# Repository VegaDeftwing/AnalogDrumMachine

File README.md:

# AnalogDrumMachine
Capstone Project @ UNL, 2020-2021

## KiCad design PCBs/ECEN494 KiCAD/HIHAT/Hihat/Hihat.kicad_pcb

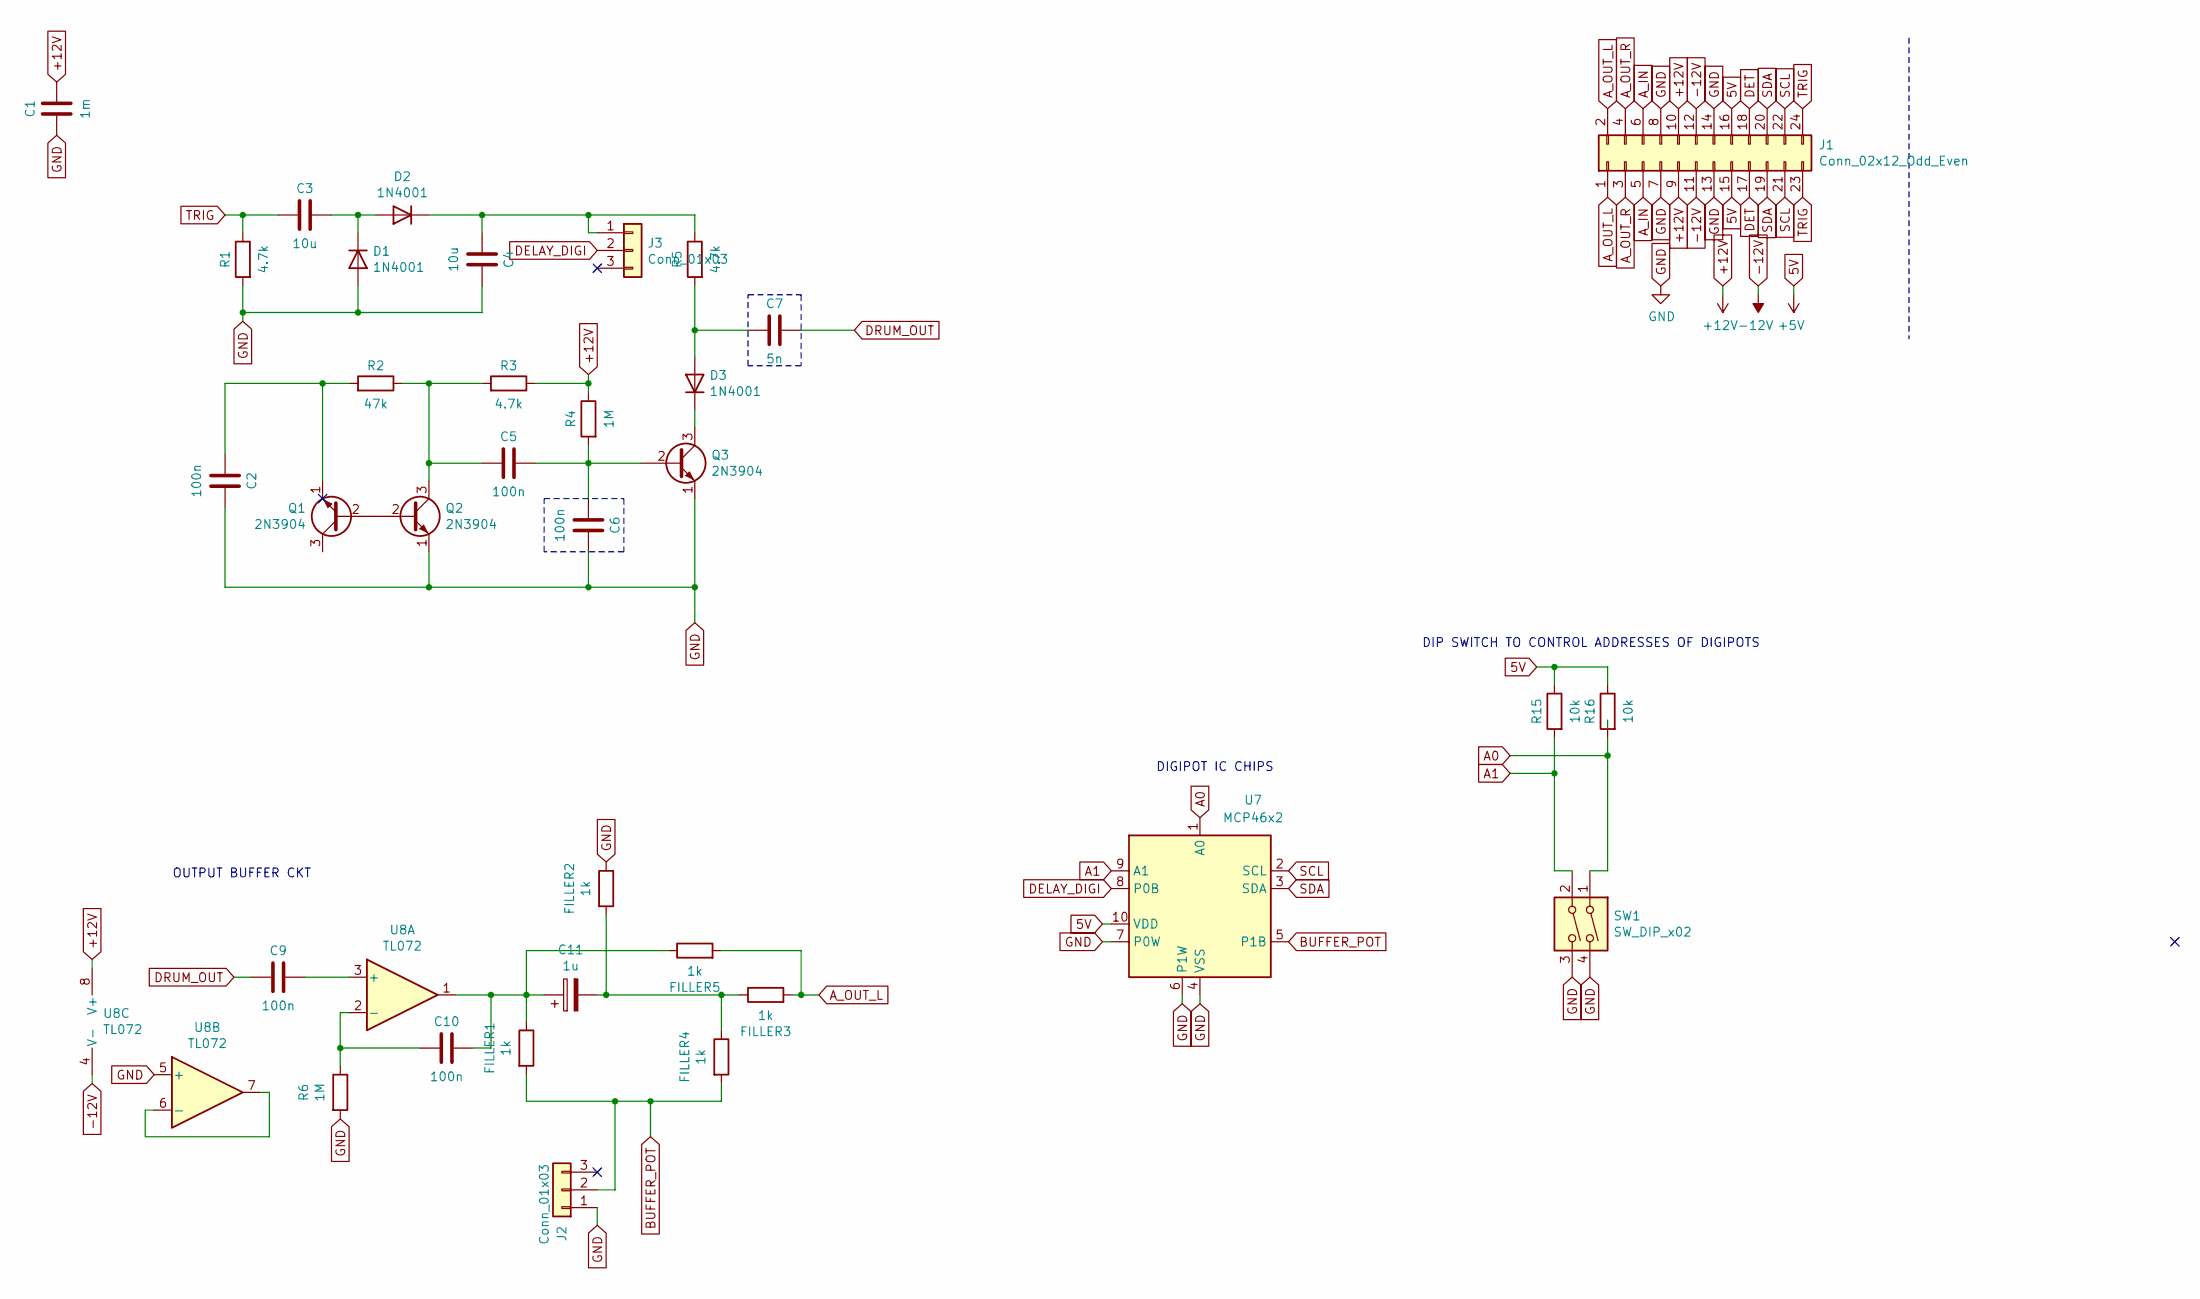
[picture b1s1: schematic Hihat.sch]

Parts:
C1: 1m; C_Disc_D7.0mm_W2.5mm_P5.00mm
C2, C5, C6, C9, C10: 100n; C_Disc_D7.0mm_W2.5mm_P5.00mm
C3, C4: 10u; C_Disc_D7.0mm_W2.5mm_P5.00mm
C7: 5n; C_Disc_D7.0mm_W2.5mm_P5.00mm
C11: 1u; C_Disc_D7.0mm_W2.5mm_P5.00mm
D1, D2, D3: 1N4001; D_DO-41_SOD81_P10.16mm_Horizontal
FILLER1, FILLER2, FILLER3, FILLER4, FILLER5: 1k; R_Axial_DIN0207_L6.3mm_D2.5mm_P10.16mm_Horizontal
J1: Conn_02x12_Odd_Even; PinSocket_2x12_P2.54mm_Vertical
J2, J3: Conn_01x03; PinSocket_1x03_P2.54mm_Vertical
Q1, Q2, Q3: 2N3904; TO-92_Inline
R1, R3, R5: 4.7k; R_Axial_DIN0207_L6.3mm_D2.5mm_P10.16mm_Horizontal
R2: 47k; R_Axial_DIN0207_L6.3mm_D2.5mm_P10.16mm_Horizontal
R4, R6: 1M; R_Axial_DIN0207_L6.3mm_D2.5mm_P10.16mm_Horizontal
R15, R16: 10k; R_Axial_DIN0207_L6.3mm_D2.5mm_P10.16mm_Horizontal
SW1: SW_DIP_x02; SW_DIP_SPSTx02_Slide_6.7x6.64mm_W7.62mm_P2.54mm_LowProfile
U7: MCP46x2; MSOP-10_3x3mm_P0.5mm
U8: TL072; SO-8_5.3x6.2mm_P1.27mm

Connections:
5V: J1.15, J1.16, R15.1, R16.1, U7.10 (VDD)
+12V: C1.2, J1.9, J1.10, R3.1, R4.1, U8.8 (V+)
-12V: J1.11, J1.12, U8.4 (V-)
A0: R16.2, SW1.1, U7.1 (A0)
A1: R15.2, SW1.2, U7.9 (A1)
A_IN: J1.5, J1.6
A_OUT_L: FILLER3.2, FILLER5.2, J1.1, J1.2
A_OUT_R: J1.3, J1.4
BUFFER_POT: FILLER1.2, FILLER4.2, J2.2, U7.5 (P1B)
DELAY_DIGI: J3.2, U7.8 (P0B)
DET: J1.17, J1.18
DRUM_OUT: C7.2, C9.1
GND: C1.1, C2.2, C4.2, C6.2, D1.2 (A), FILLER2.1, J1.7, J1.8, J1.13, J1.14, J2.1, Q2.1 (E), Q3.1 (E), R1.2, R6.2, SW1.3, SW1.4, U7.4 (VSS), U7.6 (P1W), U7.7 (P0W), U8.5 (+)
unnamed: C2.1, Q1.1 (E), R2.2
unnamed: C3.2, D1.1 (K), D2.2 (A)
unnamed: C4.1, D2.1 (K), J3.1, R5.1
unnamed: C5.1, Q2.3 (C), R2.1, R3.2
unnamed: C5.2, C6.1, Q3.2 (B), R4.2
unnamed: C7.1, D3.2 (A), R5.2
unnamed: C9.2, U8.3 (+)
unnamed: C10.1, R6.1, U8.2 (-)
unnamed: C10.2, C11.1, FILLER1.1, FILLER5.1, U8.1
unnamed: C11.2, FILLER2.2, FILLER3.1, FILLER4.1
unnamed: D3.1 (K), Q3.3 (C)
unnamed: Q1.2 (B), Q2.2 (B)
unnamed: U8.6 (-), U8.7
SCL: J1.21, J1.22, U7.2 (SCL)
SDA: J1.19, J1.20, U7.3 (SDA)
TRIG: C3.1, J1.23, J1.24, R1.1

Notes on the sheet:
OUTPUT BUFFER CKT
DIGIPOT IC CHIPS
DIP SWITCH TO CONTROL ADDRESSES OF DIGIPOTS

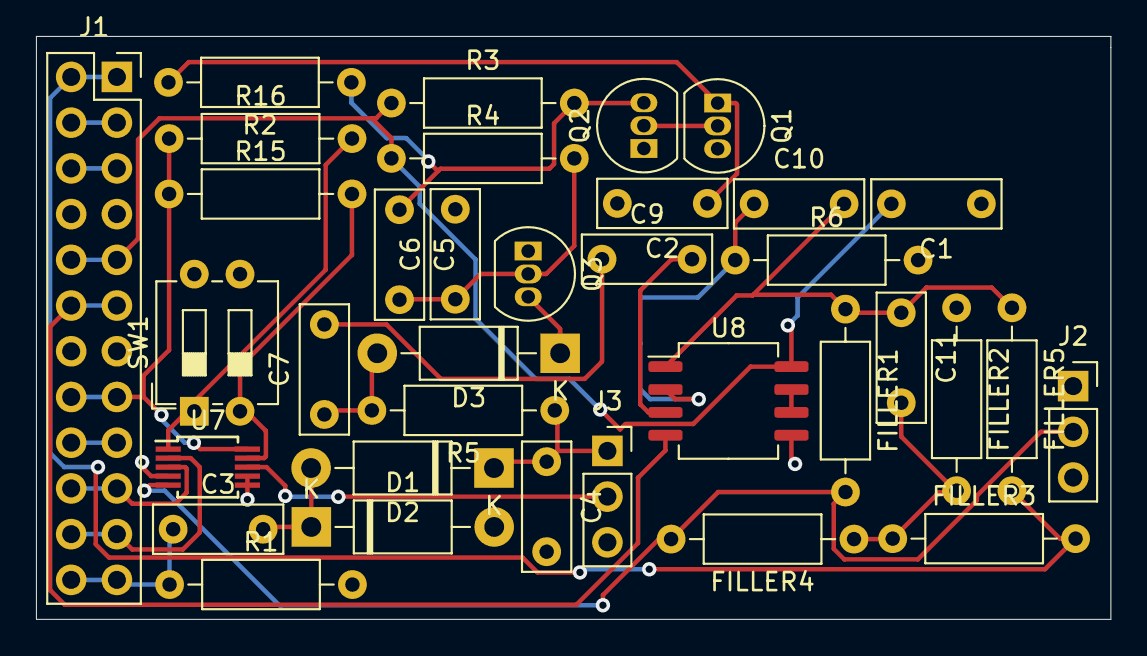
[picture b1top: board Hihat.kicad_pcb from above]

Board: 2 copper layers, 59.7 x 32.4 mm, 35 parts (0 on the bottom side), 29 nets.

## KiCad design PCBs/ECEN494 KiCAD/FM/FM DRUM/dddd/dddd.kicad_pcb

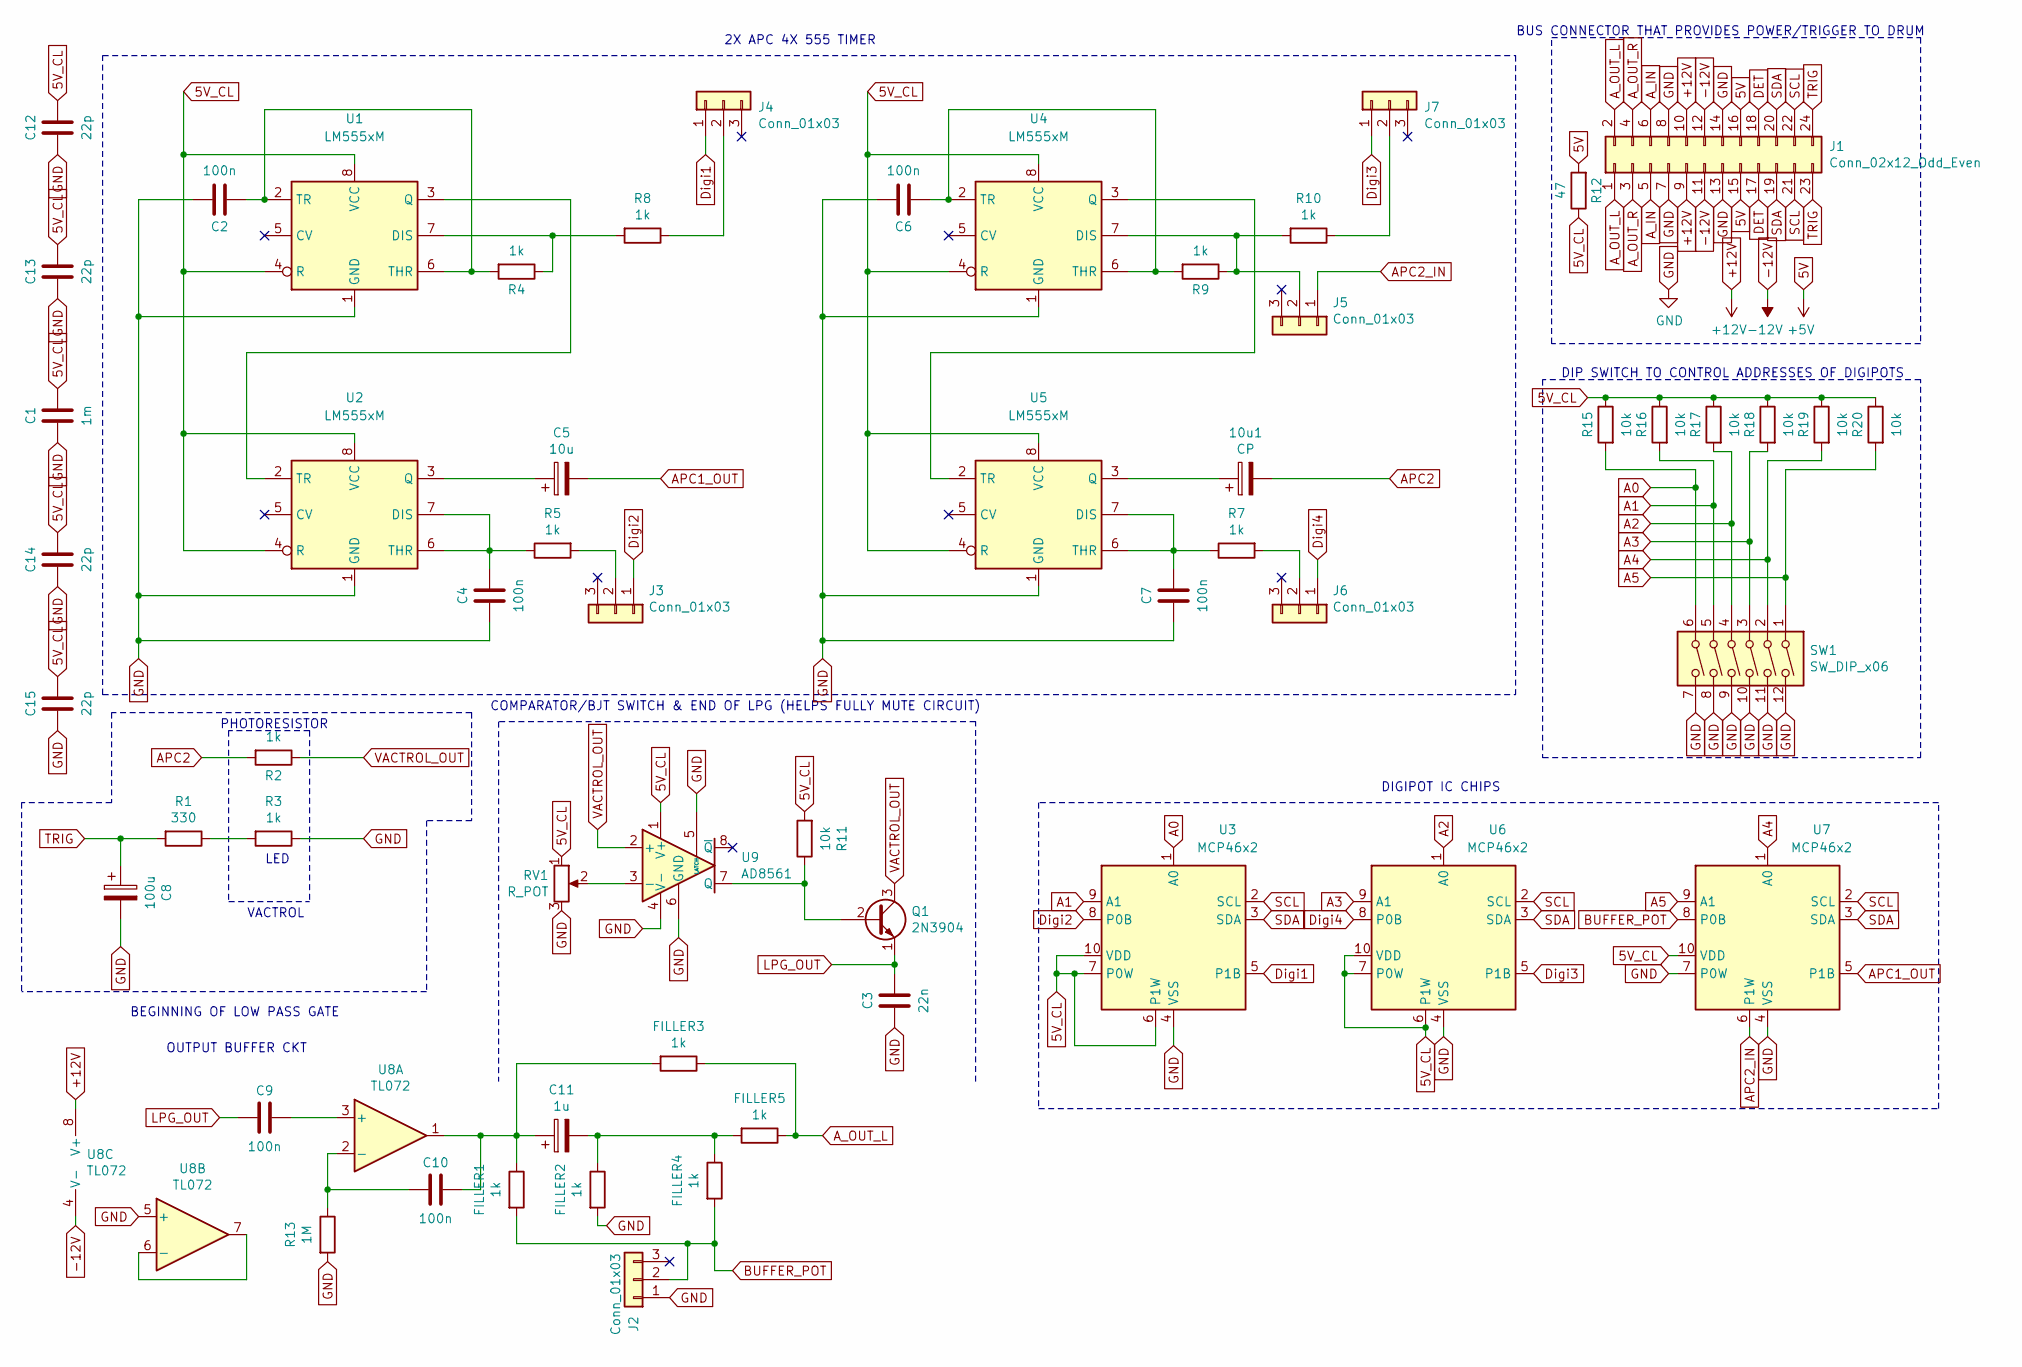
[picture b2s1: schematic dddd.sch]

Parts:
10u1: CP; C_Disc_D7.0mm_W2.5mm_P5.00mm
C1: 1m; C_Disc_D7.0mm_W2.5mm_P5.00mm
C2, C4, C6, C7, C9, C10: 100n; C_Disc_D7.0mm_W2.5mm_P5.00mm
C3: 22n; C_Disc_D7.0mm_W2.5mm_P5.00mm
C5: 10u; C_Disc_D7.0mm_W2.5mm_P5.00mm
C8: 100u; C_Disc_D7.0mm_W2.5mm_P5.00mm
C11: 1u; C_Disc_D7.0mm_W2.5mm_P5.00mm
C12, C13, C14, C15: 22p; C_Disc_D7.0mm_W2.5mm_P5.00mm
FILLER1, FILLER2, FILLER3, FILLER4, FILLER5: 1k; R_Axial_DIN0207_L6.3mm_D2.5mm_P10.16mm_Horizontal
J1: Conn_02x12_Odd_Even; PinSocket_2x12_P2.54mm_Vertical
J2, J3, J4, J5, J6, J7: Conn_01x03; PinSocket_1x03_P2.54mm_Vertical
Q1: 2N3904; PinSocket_1x03_P2.54mm_Vertical
R1: 330; R_Axial_DIN0207_L6.3mm_D2.5mm_P10.16mm_Horizontal
R2, R3, R4, R5, R7, R8, R9, R10: 1k; R_Axial_DIN0207_L6.3mm_D2.5mm_P10.16mm_Horizontal
R11, R15, R16, R17, R18, R19, R20: 10k; R_Axial_DIN0207_L6.3mm_D2.5mm_P10.16mm_Horizontal
R12: 47; R_Axial_DIN0207_L6.3mm_D2.5mm_P10.16mm_Horizontal
R13: 1M; R_Axial_DIN0207_L6.3mm_D2.5mm_P10.16mm_Horizontal
RV1: R_POT; Potentiometer_Piher_PT-6-V_Vertical
SW1: SW_DIP_x06; SW_DIP_SPSTx06_Slide_6.7x16.8mm_W7.62mm_P2.54mm_LowProfile
U1, U2, U4, U5: LM555xM; DIP-8_W7.62mm
U3, U6, U7: MCP46x2; MSOP-10_3x3mm_P0.5mm
U8: TL072; SO-8_5.3x6.2mm_P1.27mm
U9: AD8561; DIP-8_W7.62mm

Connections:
5V: J1.15, J1.16, R12.2
5V_CL: C1.2, C12.2, C13.2, C14.2, C15.2, R11.2, R12.1, R15.1, R16.1, R17.1, R18.1, R19.1, R20.1, RV1.1, U1.4 (R), U1.8 (VCC), U2.4 (R), U2.8 (VCC), U3.6 (P1W), U3.7 (P0W), U3.10 (VDD), U4.4 (R), U4.8 (VCC), U5.4 (R), U5.8 (VCC), U6.6 (P1W), U6.7 (P0W), U6.10 (VDD), U7.10 (VDD), U9.1 (V+)
+12V: J1.9, J1.10, U8.8 (V+)
-12V: J1.11, J1.12, U8.4 (V-)
A0: R15.2, SW1.6, U3.1 (A0)
A1: R16.2, SW1.5, U3.9 (A1)
A2: R17.2, SW1.4, U6.1 (A0)
A3: R18.2, SW1.3, U6.9 (A1)
A4: R19.2, SW1.2, U7.1 (A0)
A5: R20.2, SW1.1, U7.9 (A1)
APC1_OUT: C5.2, U7.5 (P1B)
APC2: 10u1.2, R2.2
APC2_IN: J5.1, U7.6 (P1W)
A_IN: J1.5, J1.6
A_OUT_L: FILLER3.1, FILLER5.1, J1.1, J1.2
A_OUT_R: J1.3, J1.4
BUFFER_POT: FILLER1.2, FILLER4.2, J2.2, U7.8 (P0B)
DET: J1.17, J1.18
Digi1: J4.1, U3.5 (P1B)
Digi2: J3.1, U3.8 (P0B)
Digi3: J7.1, U6.5 (P1B)
Digi4: J6.1, U6.8 (P0B)
GND: C1.1, C2.2, C3.1, C4.1, C6.2, C7.1, C8.2, C12.1, C13.1, C14.1, C15.1, FILLER2.2, J1.7, J1.8, J1.13, J1.14, J2.1, R3.1, R13.2, RV1.3, SW1.7, SW1.8, SW1.9, SW1.10, SW1.11, SW1.12, U1.1 (GND), U2.1 (GND), U3.4 (VSS), U4.1 (GND), U5.1 (GND), U6.4 (VSS), U7.4 (VSS), U7.7 (P0W), U8.5 (+), U9.4 (V-), U9.5 (LATCH), U9.6 (GND)
LPG_OUT: C3.2, C9.1, Q1.1 (E)
unnamed: 10u1.1, U5.3 (Q)
unnamed: C2.1, R4.2, U1.2 (TR), U1.6 (THR)
unnamed: C4.2, R5.1, U2.6 (THR), U2.7 (DIS)
unnamed: C5.1, U2.3 (Q)
unnamed: C6.1, R9.2, U4.2 (TR), U4.6 (THR)
unnamed: C7.2, R7.1, U5.6 (THR), U5.7 (DIS)
unnamed: C9.2, U8.3 (+)
unnamed: C10.1, R13.1, U8.2 (-)
unnamed: C10.2, C11.1, FILLER1.1, FILLER3.2, U8.1
unnamed: C11.2, FILLER2.1, FILLER4.1, FILLER5.2
unnamed: J3.2, R5.2
unnamed: J4.2, R8.1
unnamed: J5.2, R9.1, R10.2, U4.7 (DIS)
unnamed: J6.2, R7.2
unnamed: J7.2, R10.1
unnamed: Q1.2 (B), R11.1, U9.7 (Q)
unnamed: R1.1, R3.2
unnamed: R4.1, R8.2, U1.7 (DIS)
unnamed: RV1.2, U9.3 (-)
unnamed: U1.3 (Q), U2.2 (TR)
unnamed: U4.3 (Q), U5.2 (TR)
unnamed: U8.6 (-), U8.7
SCL: J1.21, J1.22, U3.2 (SCL), U6.2 (SCL), U7.2 (SCL)
SDA: J1.19, J1.20, U3.3 (SDA), U6.3 (SDA), U7.3 (SDA)
TRIG: C8.1, J1.23, J1.24, R1.2
VACTROL_OUT: Q1.3 (C), R2.1, U9.2 (+)

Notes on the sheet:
BEGINNING OF LOW PASS GATE
OUTPUT BUFFER CKT
PHOTORESISTOR
VACTROL
LED
COMPARATOR/BJT SWITCH & END OF LPG (HELPS FULLY MUTE CIRCUIT)
2X APC 4X 555 TIMER
DIGIPOT IC CHIPS
BUS CONNECTOR THAT PROVIDES POWER/TRIGGER TO DRUM
DIP SWITCH TO CONTROL ADDRESSES OF DIGIPOTS

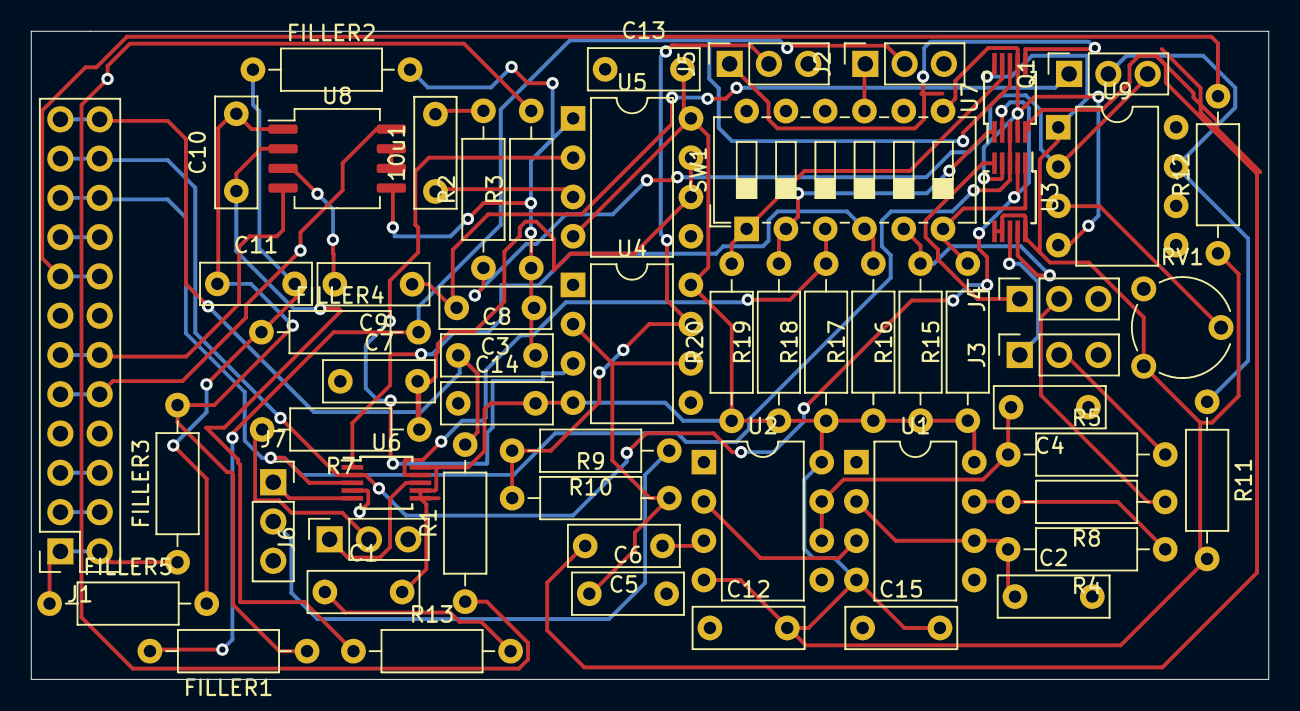
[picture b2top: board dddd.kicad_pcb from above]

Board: 2 copper layers, 80.0 x 41.9 mm, 58 parts (0 on the bottom side), 50 nets.

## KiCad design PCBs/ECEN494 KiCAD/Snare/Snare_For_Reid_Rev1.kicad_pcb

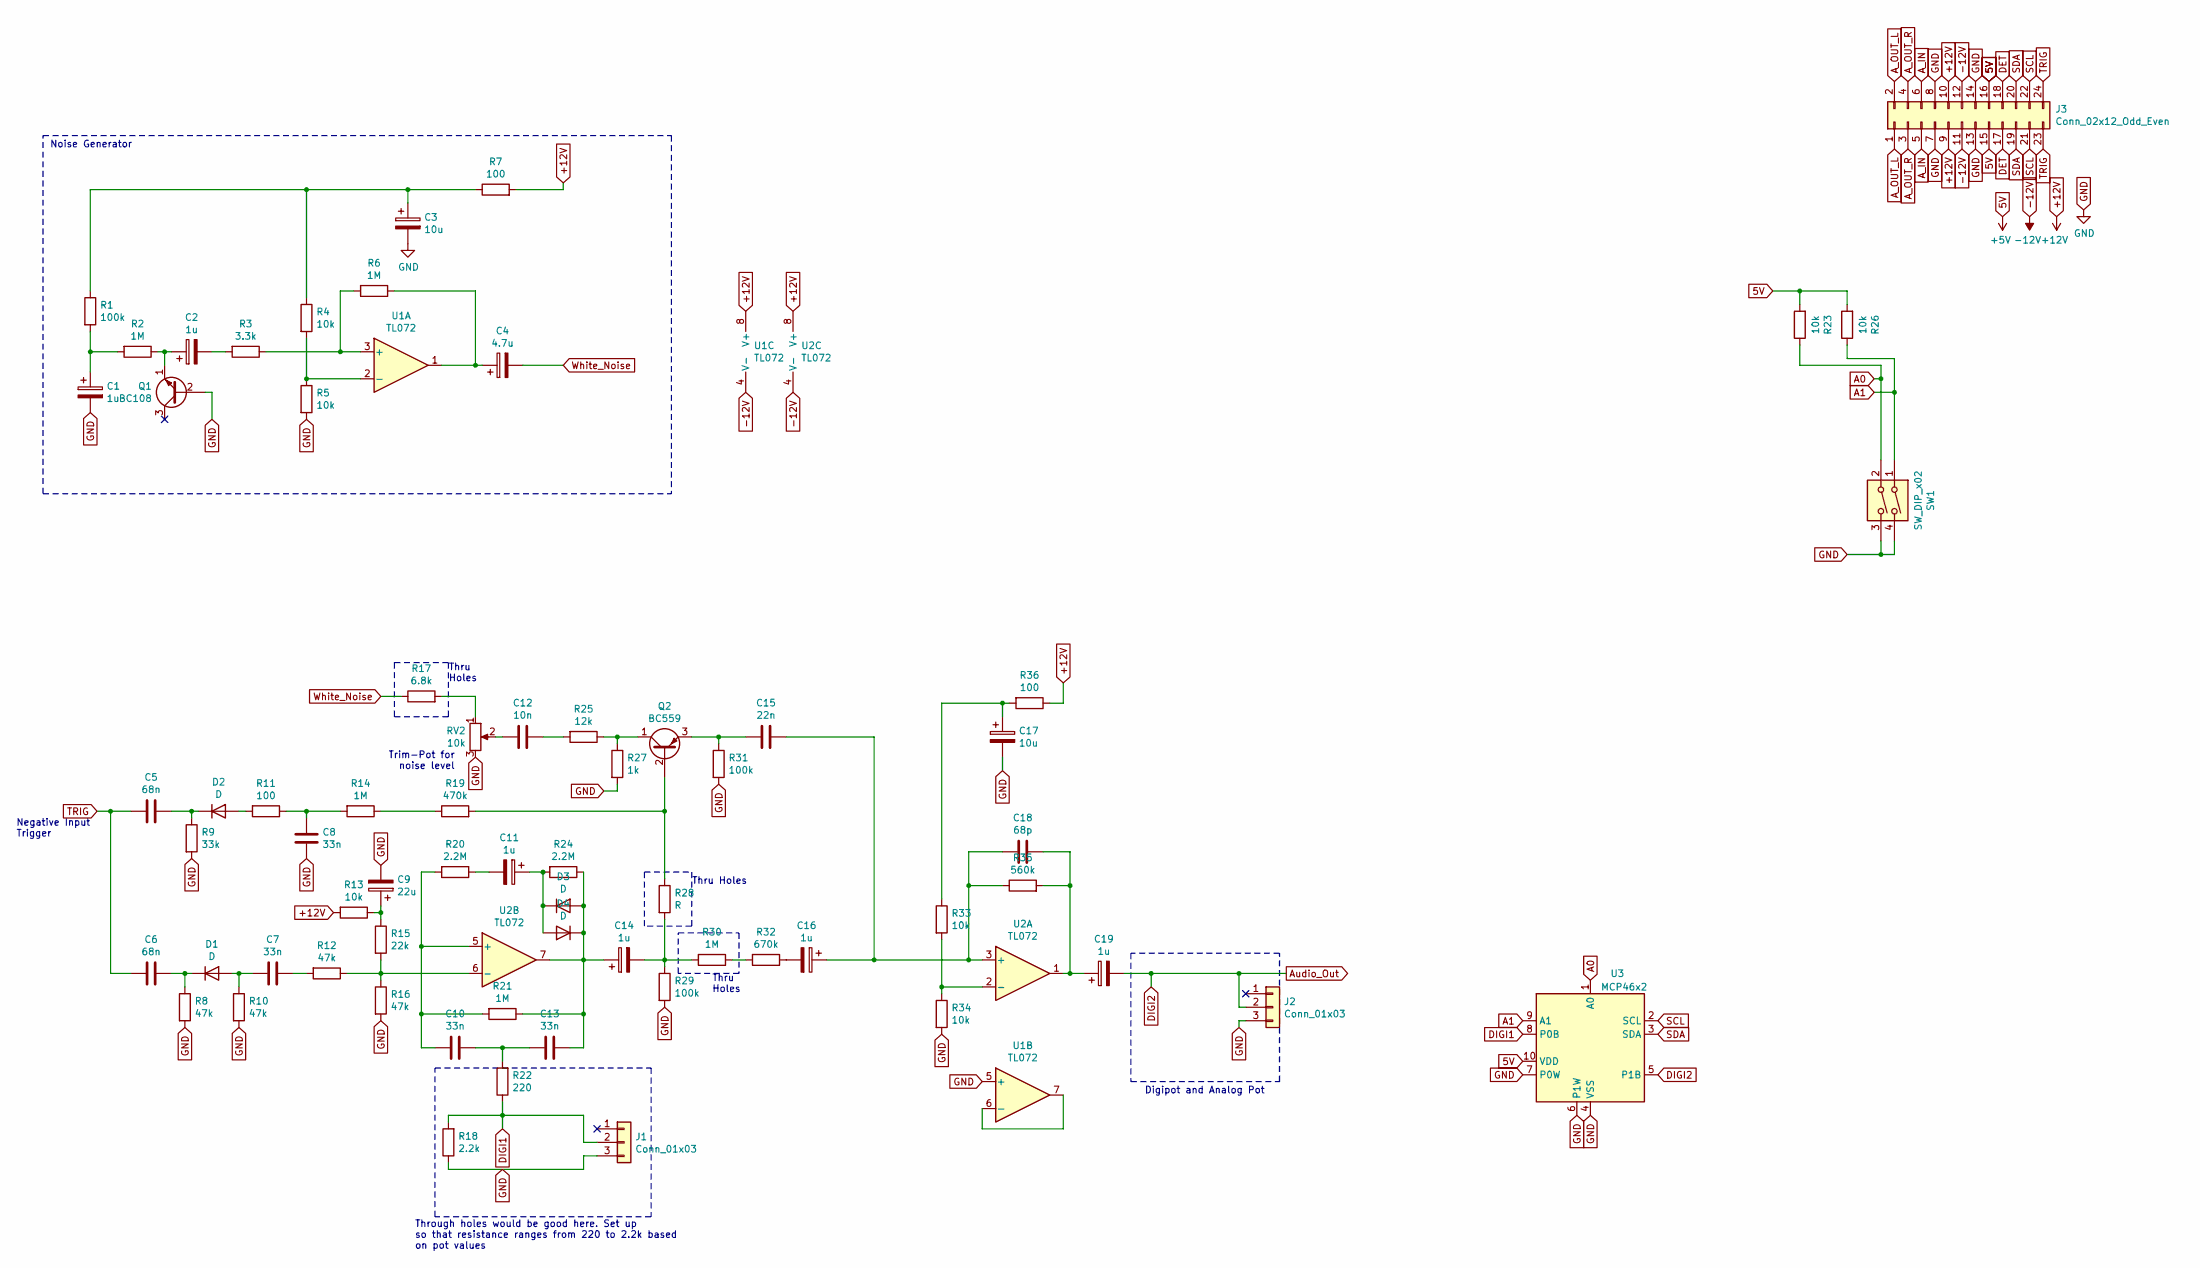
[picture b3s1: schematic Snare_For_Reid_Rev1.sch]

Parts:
C1, C2, C11, C14, C16, C19: 1u; C_Disc_D7.0mm_W2.5mm_P5.00mm
C3, C17: 10u; C_Disc_D7.0mm_W2.5mm_P5.00mm
C4: 4.7u; C_Disc_D7.0mm_W2.5mm_P5.00mm
C5, C6: 68n; C_Disc_D7.0mm_W2.5mm_P5.00mm
C7, C8, C10, C13: 33n; C_Disc_D7.0mm_W2.5mm_P5.00mm
C9: 22u; C_Disc_D7.0mm_W2.5mm_P5.00mm
C12: 10n; C_Disc_D7.0mm_W2.5mm_P5.00mm
C15: 22n; C_Disc_D7.0mm_W2.5mm_P5.00mm
C18: 68p; C_Disc_D7.0mm_W2.5mm_P5.00mm
D1, D2, D3, D4: D; R_Axial_DIN0207_L6.3mm_D2.5mm_P10.16mm_Horizontal
J1, J2: Conn_01x03; PinSocket_1x03_P2.54mm_Vertical
J3: Conn_02x12_Odd_Even; PinSocket_2x12_P2.54mm_Vertical
Q1: BC108; TO-18-3
Q2: BC559; TO-92_Inline
R1, R29, R31: 100k; R_Axial_DIN0207_L6.3mm_D2.5mm_P10.16mm_Horizontal
R2, R6, R14, R21, R30: 1M; R_Axial_DIN0207_L6.3mm_D2.5mm_P10.16mm_Horizontal
R3: 3.3k; R_Axial_DIN0207_L6.3mm_D2.5mm_P10.16mm_Horizontal
R4, R5, R13, R23, R26, R33, R34: 10k; R_Axial_DIN0207_L6.3mm_D2.5mm_P10.16mm_Horizontal
R7, R11, R36: 100; R_Axial_DIN0207_L6.3mm_D2.5mm_P10.16mm_Horizontal
R8, R10, R12, R16: 47k; R_Axial_DIN0207_L6.3mm_D2.5mm_P10.16mm_Horizontal
R9: 33k; R_Axial_DIN0207_L6.3mm_D2.5mm_P10.16mm_Horizontal
R15: 22k; R_Axial_DIN0207_L6.3mm_D2.5mm_P10.16mm_Horizontal
R17: 6.8k; R_Axial_DIN0207_L6.3mm_D2.5mm_P10.16mm_Horizontal
R18: 2.2k; R_Axial_DIN0207_L6.3mm_D2.5mm_P10.16mm_Horizontal
R19: 470k; R_Axial_DIN0207_L6.3mm_D2.5mm_P10.16mm_Horizontal
R20, R24: 2.2M; R_Axial_DIN0207_L6.3mm_D2.5mm_P10.16mm_Horizontal
R22: 220; R_Axial_DIN0207_L6.3mm_D2.5mm_P10.16mm_Horizontal
R25: 12k; R_Axial_DIN0207_L6.3mm_D2.5mm_P10.16mm_Horizontal
R27: 1k; R_Axial_DIN0207_L6.3mm_D2.5mm_P10.16mm_Horizontal
R28: R; R_Axial_DIN0207_L6.3mm_D2.5mm_P10.16mm_Horizontal
R32: 670k; R_Axial_DIN0207_L6.3mm_D2.5mm_P10.16mm_Horizontal
R35: 560k; R_Axial_DIN0207_L6.3mm_D2.5mm_P10.16mm_Horizontal
RV2: 10k; Potentiometer_Piher_PT-6-V_Vertical
SW1: SW_DIP_x02; SW_DIP_SPSTx02_Slide_6.7x6.64mm_W7.62mm_P2.54mm_LowProfile
U1, U2: TL072; SO-8_5.3x6.2mm_P1.27mm
U3: MCP46x2; MSOP-10_3x3mm_P0.5mm

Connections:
5V: J3.15, J3.16, R23.2, R26.2, U3.10 (VDD)
+12V: J3.9, J3.10, R7.2, R13.2, R36.1, U1.8 (V+), U2.8 (V+)
-12V: J3.11, J3.12, U1.4 (V-), U2.4 (V-)
A0: R23.1, SW1.2, U3.1 (A0)
A1: R26.1, SW1.1, U3.9 (A1)
A_IN: J3.5, J3.6
A_OUT_L: J3.1, J3.2
A_OUT_R: J3.3, J3.4
Audio_Out: C19.2, J2.2, U3.5 (P1B)
DET: J3.17, J3.18
DIGI1: J1.2, R18.2, R22.1, U3.8 (P0B)
GND: C1.2, C3.2, C8.2, C9.2, C17.2, J1.3, J2.3, J3.7, J3.8, J3.13, J3.14, Q1.2 (B), R5.2, R8.2, R9.2, R10.2, R16.2, R18.1, R27.2, R29.2, R31.2, R34.2, RV2.3, SW1.3, SW1.4, U1.5 (+), U3.4 (VSS), U3.6 (P1W), U3.7 (P0W)
unnamed: C1.1, R1.2, R2.2
unnamed: C2.1, Q1.1 (E), R2.1
unnamed: C2.2, R3.2
unnamed: C3.1, R1.1, R4.1, R7.1
unnamed: C4.1, R6.1, U1.1
unnamed: C5.1, D2.1 (K), R9.1
unnamed: C6.1, D1.1 (K), R8.1
unnamed: C7.1, R12.2
unnamed: C7.2, D1.2 (A), R10.1
unnamed: C8.1, R11.1, R14.2
unnamed: C9.1, R13.1, R15.1
unnamed: C10.1, C13.2, R22.2
unnamed: C10.2, R20.2, R21.2, U2.5 (+)
unnamed: C11.1, D3.1 (K), D4.2 (A), R24.2
unnamed: C11.2, R20.1
unnamed: C12.1, R25.2
unnamed: C12.2, RV2.2
unnamed: C13.1, C14.1, D3.2 (A), D4.1 (K), R21.1, R24.1, U2.7
unnamed: C14.2, R28.2, R29.1, R30.2
unnamed: C15.1, C16.1, C18.2, R35.1, U2.3 (+)
unnamed: C15.2, Q2.3 (E), R31.1
unnamed: C16.2, R32.1
unnamed: C17.1, R33.1, R36.2
unnamed: C18.1, C19.1, R35.2, U2.1
unnamed: D2.2 (A), R11.2
unnamed: Q2.1 (C), R25.1, R27.1
unnamed: Q2.2 (B), R19.2, R28.1
unnamed: R3.1, R6.2, U1.3 (+)
unnamed: R4.2, R5.1, U1.2 (-)
unnamed: R12.1, R15.2, R16.1, U2.6 (-)
unnamed: R14.1, R19.1
unnamed: R17.2, RV2.1
unnamed: R30.1, R32.2
unnamed: R33.2, R34.1, U2.2 (-)
unnamed: U1.6 (-), U1.7
SCL: J3.21, J3.22, U3.2 (SCL)
SDA: J3.19, J3.20, U3.3 (SDA)
TRIG: C5.2, C6.2, J3.23, J3.24
White_Noise: C4.2, R17.1

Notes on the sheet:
Noise Generator
Trim-Pot for noise level
Negative Input Trigger
Thru Holes
Thru Holes
Through holes would be good here. Set up so that resistance ranges from 220 to 2.2k based on pot values
Thru Holes
Digipot and Analog Pot

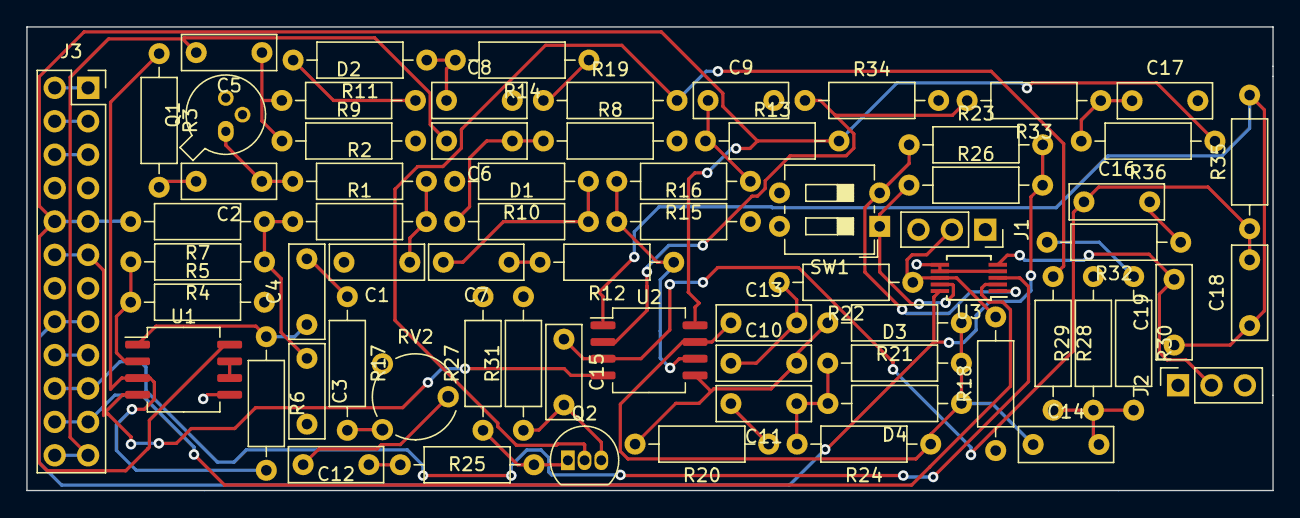
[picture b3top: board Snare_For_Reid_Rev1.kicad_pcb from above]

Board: 2 copper layers, 94.8 x 35.2 mm, 69 parts (0 on the bottom side), 51 nets.

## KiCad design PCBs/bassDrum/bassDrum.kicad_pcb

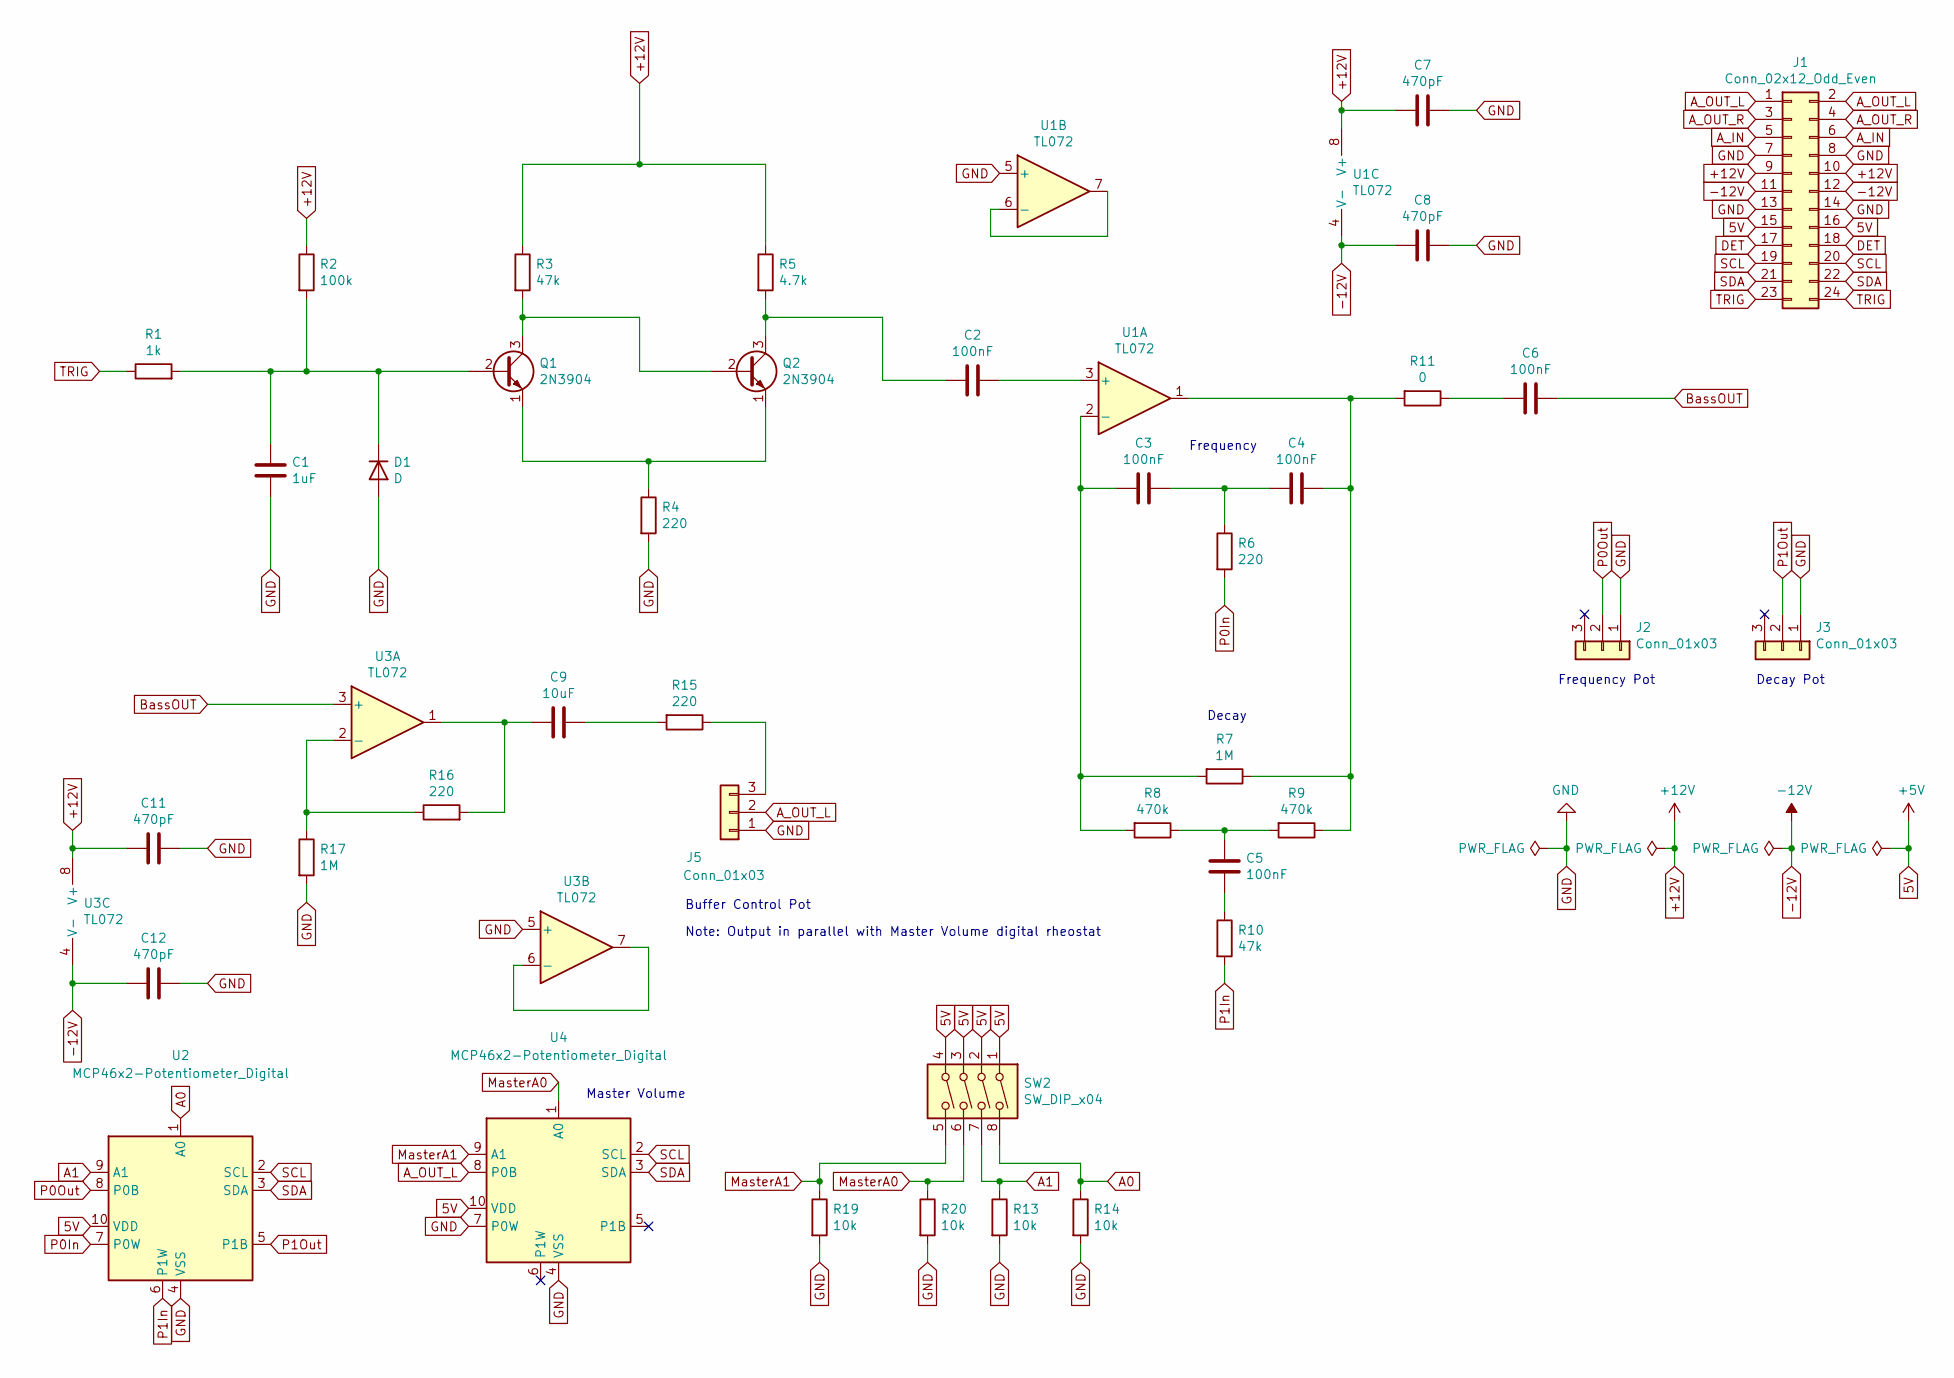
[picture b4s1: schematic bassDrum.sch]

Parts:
C1: 1uF; C_0805_2012Metric
C2, C3, C4, C5, C6: 100nF; C_0805_2012Metric
C7, C8, C11, C12: 470pF; C_0805_2012Metric
C9: 10uF; C_0805_2012Metric
D1: D; D_DO-41_SOD81_P7.62mm_Horizontal
J1: Conn_02x12_Odd_Even; PinHeader_2x12_P2.54mm_Vertical
J2, J3, J5: Conn_01x03; PinHeader_1x03_P2.54mm_Vertical
Q1, Q2: 2N3904; TO-92_Inline
R1: 1k; R_0805_2012Metric
R2: 100k; R_0805_2012Metric
R3, R10: 47k; R_0805_2012Metric
R4, R6, R15, R16: 220; R_0805_2012Metric
R5: 4.7k; R_0805_2012Metric
R7, R17: 1M; R_0805_2012Metric
R8, R9: 470k; R_0805_2012Metric
R11: 0; R_0805_2012Metric
R13, R14, R19, R20: 10k; R_0805_2012Metric
SW2: SW_DIP_x04; SW_DIP_SPSTx04_Slide_6.7x11.72mm_W7.62mm_P2.54mm_LowProfile
U1, U3: TL072; SO-8_5.3x6.2mm_P1.27mm
U2, U4: MCP46x2-Potentiometer_Digital; MSOP-10_3x3mm_P0.5mm

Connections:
5V: J1.15, J1.16, SW2.1, SW2.2, SW2.3, SW2.4, U2.10 (VDD), U4.10 (VDD)
+12V: C7.2, C11.2, J1.9, J1.10, R2.1, R3.1, R5.1, U1.8 (V+), U3.8 (V+)
-12V: C8.2, C12.2, J1.11, J1.12, U1.4 (V-), U3.4 (V-)
A0: R14.1, SW2.8, U2.1 (A0)
A1: R13.1, SW2.7, U2.9 (A1)
A_IN: J1.5, J1.6
A_OUT_L: J1.1, J1.2, J5.2, U4.8 (P0B)
A_OUT_R: J1.3, J1.4
BassOUT: C6.1, U3.3 (+)
DET: J1.17, J1.18
GND: C1.2, C7.1, C8.1, C11.1, C12.1, D1.2 (A), J1.7, J1.8, J1.13, J1.14, J2.1, J3.1, J5.1, R4.2, R13.2, R14.2, R17.2, R19.2, R20.2, U1.5 (+), U2.4 (VSS), U3.5 (+), U4.4 (VSS), U4.7 (P0W)
MasterA0: R20.1, SW2.6, U4.1 (A0)
MasterA1: R19.1, SW2.5, U4.9 (A1)
unnamed: C1.1, D1.1 (K), Q1.2 (B), R1.2, R2.2
unnamed: C2.1, Q2.3 (C), R5.2
unnamed: C2.2, U1.3 (+)
unnamed: C3.1, R7.2, R8.2, U1.2 (-)
unnamed: C3.2, C4.1, R6.1
unnamed: C4.2, R7.1, R9.1, R11.2, U1.1
unnamed: C5.1, R8.1, R9.2
unnamed: C5.2, R10.1
unnamed: C6.2, R11.1
unnamed: C9.1, R15.2
unnamed: C9.2, R16.2, U3.1
unnamed: J5.3, R15.1
unnamed: Q1.1 (E), Q2.1 (E), R4.1
unnamed: Q1.3 (C), Q2.2 (B), R3.2
unnamed: R16.1, R17.1, U3.2 (-)
unnamed: U1.6 (-), U1.7
unnamed: U3.6 (-), U3.7
P0In: R6.2, U2.7 (P0W)
P0Out: J2.2, U2.8 (P0B)
P1In: R10.2, U2.6 (P1W)
P1Out: J3.2, U2.5 (P1B)
SCL: J1.19, J1.20, U2.2 (SCL), U4.2 (SCL)
SDA: J1.21, J1.22, U2.3 (SDA), U4.3 (SDA)
TRIG: J1.23, J1.24, R1.1

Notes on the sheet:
Decay
Frequency
Buffer Control Pot
Decay Pot
Frequency Pot
Master Volume
Note: Output in parallel with Master Volume digital rheostat

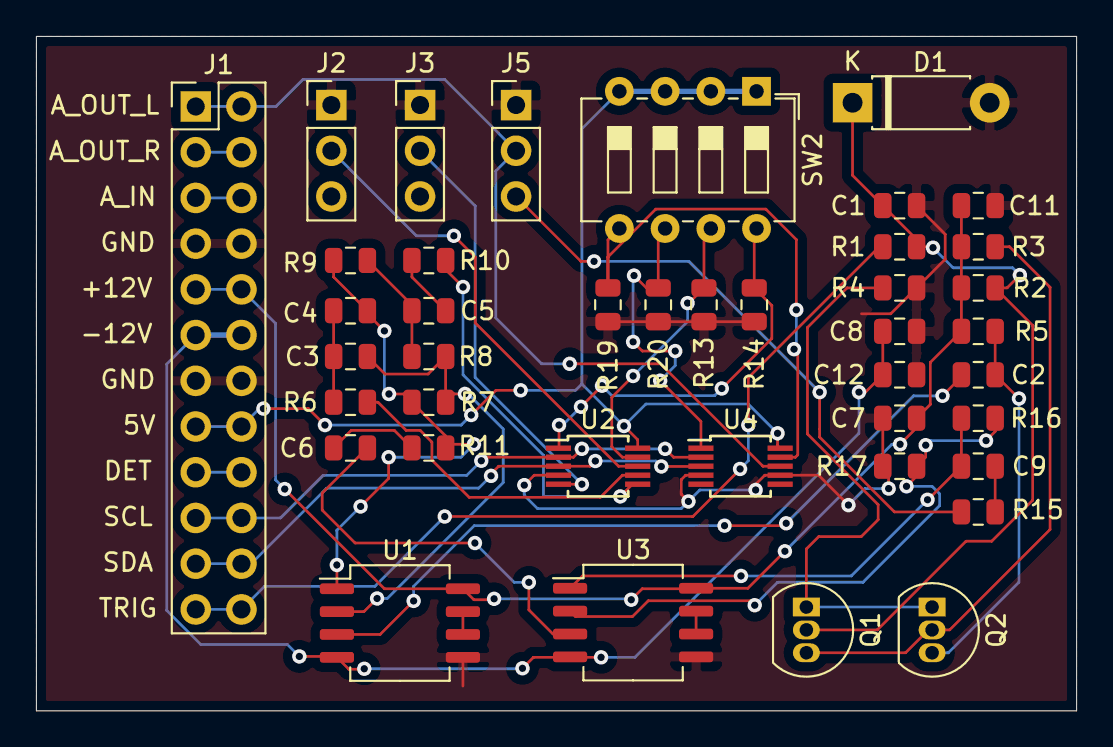
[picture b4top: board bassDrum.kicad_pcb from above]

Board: 2 copper layers, 57.8 x 37.5 mm, 41 parts (0 on the bottom side), 37 nets.

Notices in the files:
parts and their libraries:
Copyright 2021 Accelerated Designs. All rights reserved.
